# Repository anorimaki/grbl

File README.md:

***
PIC18 and ESP32 port of [Grbl project](https://github.com/gnea/grbl)

***

## State
- PIC18F26K80: Under construction (but working)
- ESP32: Under construction (but working)

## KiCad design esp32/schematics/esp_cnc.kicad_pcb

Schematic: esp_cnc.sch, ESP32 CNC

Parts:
A1, A2, A3: Pololu_Breakout_A4988; Pololu_Breakout-16_15.2x20.3mm
C1, C3: 1n; C_Disc_D5.0mm_W2.5mm_P5.00mm
C2: 10u; CP_Radial_D5.0mm_P2.00mm
C4, C5, C8, C9: 100u; CP_Radial_D8.0mm_P3.50mm
C6, C7: 22p; C_Disc_D5.0mm_W2.5mm_P5.00mm
C10: 100n; C_Disc_D5.0mm_W2.5mm_P5.00mm
D1: Red LED; LED_D3.0mm
J1: Conn_01x02; TerminalBlock_bornier-2_P5.08mm
J2: Outputs; PinHeader_2x04_P2.54mm_Vertical
J3: X Microstep; PinHeader_2x03_P2.54mm_Vertical
J4: Inputs; PinHeader_2x04_P2.54mm_Vertical
J5: USB_B_Micro; micro_usb_breakout
J6: Limits; PinHeader_2x03_P2.54mm_Vertical
J7: X Motor; PinHeader_1x04_P2.54mm_Vertical
J8: Limits Sel; PinHeader_1x03_P2.54mm_Vertical
J9: Y Microstep; PinHeader_2x03_P2.54mm_Vertical
J10: Y Motor; PinHeader_1x04_P2.54mm_Vertical
J11: Z Microstep; PinHeader_2x03_P2.54mm_Vertical
J12: Z Motor; PinHeader_1x04_P2.54mm_Vertical
Q1, Q2: BC547; TO-92_Inline
R1, R4, R5, R6: 12K; R_Axial_DIN0207_L6.3mm_D2.5mm_P10.16mm_Horizontal
R2: 680; R_Axial_DIN0207_L6.3mm_D2.5mm_P10.16mm_Horizontal
R3: 470; R_Axial_DIN0207_L6.3mm_D2.5mm_P10.16mm_Horizontal
SW1: Reset; SW_PUSH_6mm
U1: ESP32-WROOM; ESP32-WROOM-32_LARGE_PADS
U2: LM1117-3.3; TO-220-3_Horizontal_TabDown
U3: CH340G; SOP-16_4.4x10.4mm_P1.27mm
Y1: 12Mhz; Crystal_HC49-U_Vertical

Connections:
/DTR: Q2.3, R5.2, U3.13
/RTS: Q1.3, R6.2, U3.14
COOLANT_FLOOD: J2.2, U1.27
COOLANT_MIST: J2.4, U1.28
CTRL_CYCLE_START: J4.6, U1.37
CTRL_FEED_HOLD: J4.4, U1.36
CTRL_RESET: J4.2, U1.33
EN: A1.9, A2.9, A3.9, R4.1, U1.9
ESP_EN: C1.1, Q1.1, R1.2, R3.1, U1.3
GND: A1.1, A1.7, A2.1, A2.7, A3.1, A3.7, C1.2, C2.2, C3.2, C4.2, C5.2, C6.2, C7.2, C8.2, C9.2, C10.2, D1.1, J1.2, J2.1, J2.3, J2.5, J2.7, J4.1, J4.3, J4.5, J4.7, J5.5, J8.3, SW1.1, U1.1, U1.15, U1.38, U1.39, U2.1 (GND), U3.1
GPIO_0: Q2.1, U1.25
unnamed: A1.3, J7.1
unnamed: A1.4, J7.2
unnamed: A1.5, J7.3
unnamed: A1.6, J7.4
unnamed: A1.10, J3.6
unnamed: A1.11, J3.4
unnamed: A1.12, J3.2
unnamed: A1.13, A1.14
unnamed: A2.3, J10.1
unnamed: A2.4, J10.2
unnamed: A2.5, J10.3
unnamed: A2.6, J10.4
unnamed: A2.10, J9.6
unnamed: A2.11, J9.4
unnamed: A2.12, J9.2
unnamed: A2.13, A2.14
unnamed: A3.3, J12.1
unnamed: A3.4, J12.2
unnamed: A3.5, J12.3
unnamed: A3.6, J12.4
unnamed: A3.10, J11.6
unnamed: A3.11, J11.4
unnamed: A3.12, J11.2
unnamed: A3.13, A3.14
unnamed: C3.1, R3.2, SW1.2
unnamed: C6.1, U3.7, Y1.2
unnamed: C7.1, U3.8, Y1.1
unnamed: D1.2, R2.2
unnamed: J5.2, U3.6
unnamed: J5.3, U3.5
unnamed: J6.1, J6.3, J6.5, J8.2
unnamed: Q1.2, R5.1
unnamed: Q2.2, R6.1
PROBE: J4.8, U1.8
RX: U1.34, U3.2
SPINDLE_DIR: J2.6, U1.30
SPINDLE_EN: J2.8, U1.31
TX: U1.35, U3.3
VDD: A1.2, A2.2, A3.2, C4.1, C10.1, J3.1, J3.3, J3.5, J8.1, J9.1, J9.3, J9.5, J11.1, J11.3, J11.5, R1.1, R4.2, U1.2, U2.2 (VO), U3.4, U3.16
VMOT: A1.8, A2.8, A3.8, C5.1, C8.1, C9.1, J1.1
X_DIR: A1.16, U1.10
X_LIMIT: J6.2, U1.24
X_STEP: A1.15, U1.13
Y_DIR: A2.16, U1.11
Y_LIMIT: J6.4, U1.26
Y_STEP: A2.15, U1.14
Z_DIR: A3.16, U1.12
Z_LIMIT: J6.6, U1.29
Z_STEP: A3.15, U1.16
~: C2.1, J5.1, R2.1, U2.3 (VI)

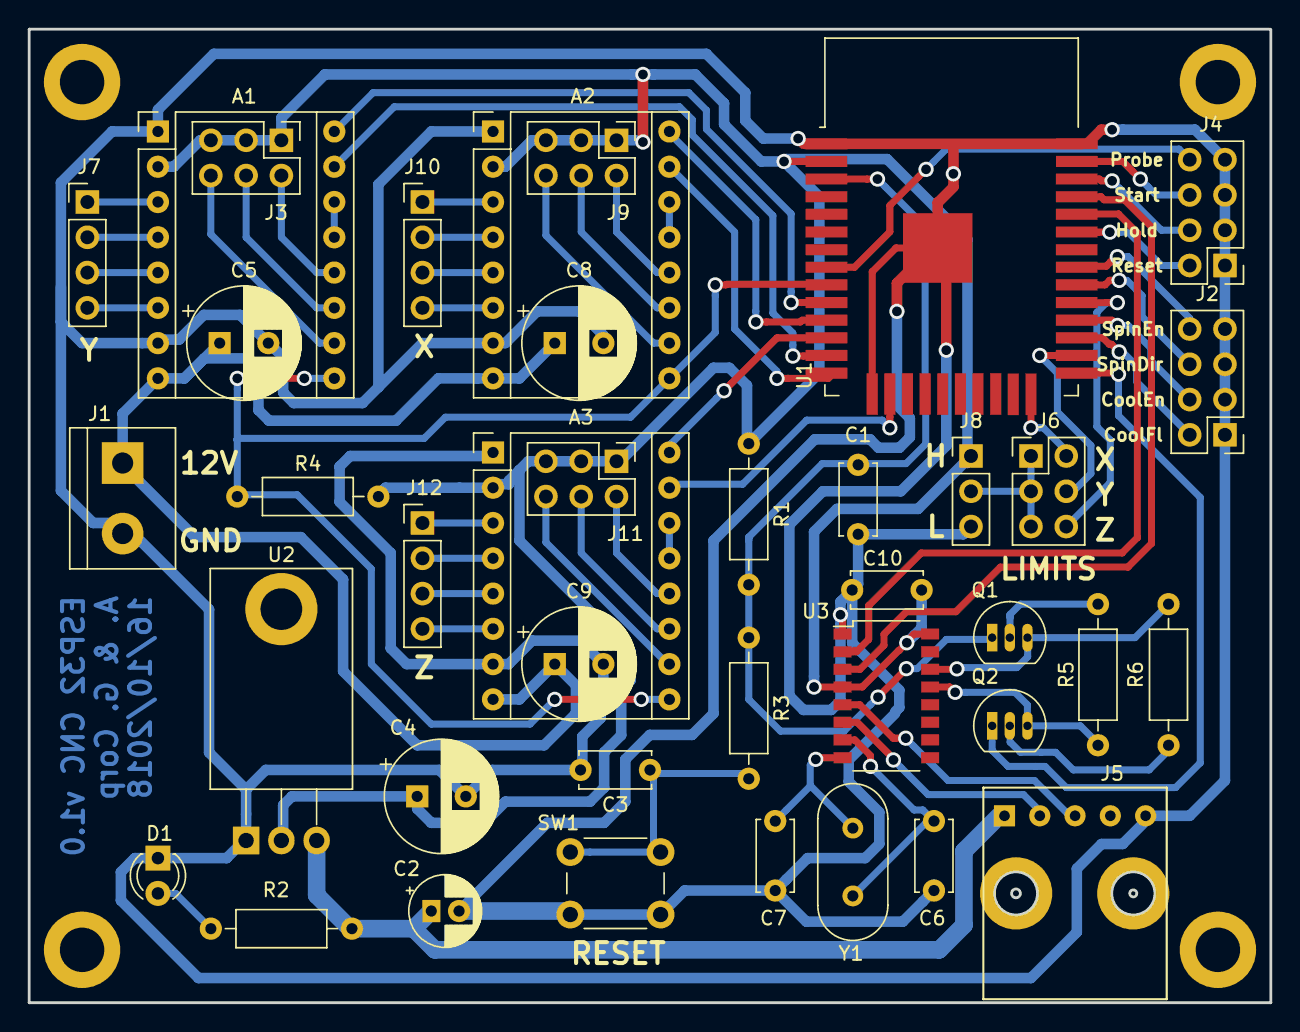
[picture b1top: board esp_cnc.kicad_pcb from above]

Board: 2 copper layers, 89.4 x 70.1 mm, 39 parts (0 on the bottom side), 61 nets.

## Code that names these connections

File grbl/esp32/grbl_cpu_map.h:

#ifndef ESP32_CPU_MAP_H
#define ESP32_CPU_MAP_H

// Define step pulse output pins. NOTE: All step bit pins must be on the same byte.
#define STEP_DDR        1			//fourth byte
#define STEP_PORT		STEP_DDR
#define X_STEP_BIT      6  // GPIO 14
#define Y_STEP_BIT      4  // GPIO 12
#define Z_STEP_BIT      5  // GPIO 13 
#define STEP_MASK       ((1ULL<<X_STEP_BIT)|(1ULL<<Y_STEP_BIT)|(1ULL<<Z_STEP_BIT)) // All step bits

  // Define step direction output pins. NOTE: All direction pins must be on the same byte.
#define DIRECTION_DDR     3			//Second byte
#define DIRECTION_PORT    DIRECTION_DDR
#define X_DIRECTION_BIT   1  	// GPIO 25
#define Y_DIRECTION_BIT   2  	// GPIO 26
#define Z_DIRECTION_BIT   3  	// GPIO 27
#define DIRECTION_MASK    ((1ULL<<X_DIRECTION_BIT)|(1ULL<<Y_DIRECTION_BIT)|(1ULL<<Z_DIRECTION_BIT)) 

  // Define stepper driver enable/disable output pin.
#define STEPPERS_DISABLE_DDR    4
#define STEPPERS_DISABLE_PORT   STEPPERS_DISABLE_DDR
#define STEPPERS_DISABLE_BIT    1  // GPIO 33
#define STEPPERS_DISABLE_MASK   (1ULL<<STEPPERS_DISABLE_BIT)

// Define homing/hard limit switch input pins and limit interrupt vectors.
// NOTE: All limit bit pins must be on the same byte, but not on a byte with other input pins (CONTROL).
#define LIMIT_DDR		0			//fifth byte
#define LIMIT_PORT		LIMIT_DDR		
#define LIMIT_PIN		LIMIT_DDR
#define X_LIMIT_BIT		0  	// GPIO 0
#define Y_LIMIT_BIT		4  	// GPIO 4
#ifdef VARIABLE_SPINDLE // Z Limit pin and spindle enabled swapped to access hardware PWM on Pin 11.
	#define Z_LIMIT_BIT		5 	// GPIO 5
#else
	#define Z_LIMIT_BIT		5	// GPIO 5
#endif
#define LIMIT_MASK		((1ULL<<X_LIMIT_BIT)|(1ULL<<Y_LIMIT_BIT)|(1ULL<<Z_LIMIT_BIT))

 // Define spindle enable and spindle direction output pins.
#define SPINDLE_ENABLE_DDR    2
#define SPINDLE_ENABLE_PORT   SPINDLE_ENABLE_DDR
// Z Limit pin and spindle PWM/enable pin swapped to access hardware PWM on Pin 11.
#ifdef VARIABLE_SPINDLE
	#ifdef USE_SPINDLE_DIR_AS_ENABLE_PIN
		// If enabled, spindle direction pin now used as spindle enable, while PWM remains on D11.
		#define SPINDLE_ENABLE_BIT    3 	// GPIO 19
	#else
		#define SPINDLE_ENABLE_BIT    3 	// GPIO 19
	#endif
#else
	#define SPINDLE_ENABLE_BIT    3 	// GPIO 19
#endif
#ifndef USE_SPINDLE_DIR_AS_ENABLE_PIN
	#define SPINDLE_DIRECTION_DDR   2
	#define SPINDLE_DIRECTION_PORT  SPINDLE_DIRECTION_DDR
	#define SPINDLE_DIRECTION_BIT   2  // GPIO 18
#endif

// Define flood and mist coolant enable output pins.
#define COOLANT_FLOOD_DDR  2
#define COOLANT_FLOOD_PORT COOLANT_FLOOD_DDR
#define COOLANT_FLOOD_BIT  0	// GPIO 16
#define COOLANT_MIST_DDR   2
#define COOLANT_MIST_PORT  COOLANT_MIST_DDR
#define COOLANT_MIST_BIT   1	// GPIO 17

// Define user-control controls (cycle start, reset, feed hold) input pins.
// NOTE: All CONTROLs pins must be on the same byte and not on a byte with other input pins (limits).
#define CONTROL_DDR       2
#define CONTROL_PIN       CONTROL_DDR
#define CONTROL_PORT      CONTROL_DDR
#define CONTROL_RESET_BIT         5  // GPIO 21
#define CONTROL_FEED_HOLD_BIT     6  // GPIO 22
#define CONTROL_CYCLE_START_BIT   7  // GPIO 23
#define CONTROL_SAFETY_DOOR_BIT   6  // GPIO 22 NOTE: Safety door is shared with feed hold. Enabled by config define.
//#define CONTROL_INT       PCIE1  // Pin change interrupt enable pin
//#define CONTROL_INT_vect  PCINT1_vect
//#define CONTROL_PCMSK     PCMSK1 // Pin change interrupt register
#define CONTROL_MASK      ((1ULL<<CONTROL_RESET_BIT)|(1ULL<<CONTROL_FEED_HOLD_BIT)|(1ULL<<CONTROL_CYCLE_START_BIT)|(1<<CONTROL_SAFETY_DOOR_BIT))
#define CONTROL_INVERT_MASK   CONTROL_MASK // May be re-defined to only invert certain control pins.

// Define probe switch input pin.
#define PROBE_DDR       4
#define PROBE_PIN       PROBE_DDR
#define PROBE_PORT      PROBE_DDR
#define PROBE_BIT       0  // GPIO 32
#define PROBE_MASK      (1ULL<<PROBE_BIT)

// Variable spindle configuration below. Do not change unless you know what you are doing.
// NOTE: Only used when variable spindle is enabled.
#define SPINDLE_PWM_MAX_VALUE     255 // Don't change. 328p fast PWM mode fixes top value as 255.
#ifndef SPINDLE_PWM_MIN_VALUE
#define SPINDLE_PWM_MIN_VALUE   1   // Must be greater than zero.
#endif
#define SPINDLE_PWM_OFF_VALUE     0
#define SPINDLE_PWM_RANGE         (SPINDLE_PWM_MAX_VALUE-SPINDLE_PWM_MIN_VALUE)
//#define SPINDLE_TCCRA_REGISTER	  TCCR2A
//#define SPINDLE_TCCRB_REGISTER	  TCCR2B
//#define SPINDLE_OCR_REGISTER      CCPR2L
//#define SPINDLE_COMB_BIT	        COM2A1

// Prescaled, 8-bit Fast PWM mode.
//#define SPINDLE_TCCRA_INIT_MASK   ((1<<WGM20) | (1<<WGM21))  // Configures fast PWM mode.
// #define SPINDLE_TCCRB_INIT_MASK   (1<<CS20)               // Disable prescaler -> 62.5kHz
// #define SPINDLE_TCCRB_INIT_MASK   (1<<CS21)               // 1/8 prescaler -> 7.8kHz (Used in v0.9)
// #define SPINDLE_TCCRB_INIT_MASK   ((1<<CS21) | (1<<CS20)) // 1/32 prescaler -> 1.96kHz
//#define SPINDLE_TCCRB_INIT_MASK      (1<<CS22)               // 1/64 prescaler -> 0.98kHz (J-tech laser)

// NOTE: On the 328p, these must be the same as the SPINDLE_ENABLE settings.
#define SPINDLE_PWM_DDR	  SPINDLE_ENABLE_DDR
#define SPINDLE_PWM_PORT  SPINDLE_PWM_DDR
#define SPINDLE_PWM_BIT	  SPINDLE_ENABLE_BIT

#endif

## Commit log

2018-06-02 - Primera versión de prueba para PIC18f26k80
2018-06-04 Reordenación de ficheros.
2018-07-28 - Comenzada adaptación a ESP32
2018-07-28 - Continuado HAL para esp32: Añadida compatibilidad con eeprom
2018-07-29 - Primera versión funcional para esp32
2018-07-29 - Adaptado hal de PIC18F26K80 a la nueva API
2018-09-08 - Comenzada comunicación por wifi con el esp32
2018-12-20 - Porting a ESP32 completado
    - PCB para prueba con ESP32
